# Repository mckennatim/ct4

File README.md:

# setup

```python
import pandas as pd
from importlib import reload
import matplotlib.pyplot as plt
import numpy as np
from IPython.display import display

```

# ct4 ads1115

Design a 4 CT energy monitor for 4 circuits. On hand are a number of 15A/1v and 20A/1v current transformers. When the CT has that kind of designation, the burden resistor is already included. (If not calculate burden resistor below in `ref`)

## ref

* [CT Sensors - Interfacing with an Arduino -OpenEnergyMonitor](https://docs.openenergymonitor.org/electricity-monitoring/ct-sensors/interface-with-arduino.html)
* [Emon Lib - OpenEnergyMonitor](https://github.com/openenergymonitor/EmonLib)
* [KiCad templates for board manufacturers](https://github.com/sethhillbrand/kicad_templates)
* [Esp32-DevKit-V1-DOIT Kicad sym & pretty mod](https://github.com/syauqibilfaqih/ESP32-DevKit-V1-DOIT?tab=readme-ov-file)
* [How to use ADS1115 16 bit ADC module with ESP32](https://www.perceptive-ic.com/news-detailed/How-to-use-ADS1115-16-bit-ADC-module-with-ESP32)

**Best Resources for Explanation:**

1. **Electronics Textbooks:**
   - "The Art of Electronics" by Horowitz & Hill (Chapter 1)
   - "Practical Electronics for Inventors" by Paul Scherz

2. **Online Resources:**
   - **All About Circuits** (allaboutcircuits.com) - Has excellent free tutorials on capacitive reactance and AC coupling
   - **Electronics Tutorials** (electronics-tutorials.ws) - Great explanations with diagrams
   - **Khan Academy** - Physics section on capacitors and RC circuits
   - **MIT OpenCourseWare** - Circuit theory courses

3. **YouTube Channels:**
   - ElectroBOOM
   - EEVblog
   - GreatScott! 

# Circuit
## parts
* esp32 devkit v1 30 pin - (DOIT)
per CT
* [CT SCT013 5A/1v](https://www.amazon.com/dp/B0C33N6NBS?ref_=ppx_hzsearch_conn_dt_b_fed_asin_title_1&th=1)
* [3.5mm audio jack socket 3pin](https://www.amazon.com/dp/B07KY7XX34?ref=ppx_yo2ov_dt_b_fed_asin_title&th=1)
* [10uf ceramic capacitor](https://www.amazon.com/dp/B0D2GVNDHY?ref=ppx_yo2ov_dt_b_fed_asin_title)
* (2)10k Resistor 10k (10k-470K)
* 1.2K Resistor
* 1K resistor
* [4 PCS ADS1115 16 Bit 16 Byte 4 Channel I2C IIC Analog-to-Digital ADC PGA Converter with Programmable Gain Amplifier](https://www.amazon.com/Qoroos-Converter-Programmable-Amplifier-Development/dp/B0DP43DDZG/ref=sr_1_3?crid=1N2VN2M5C7SEH&dib=eyJ2IjoiMSJ9.AjSKy21MIMxKduv00iytPPR8ImZpgHmwBb5A1cFqscTxcAdnr2o4j2pA87-oJvZMAupVzJ1cZdaBISYqlmQK72bHAzZvHIu_Ul1BXsxr0Ga47gktMtuJMsw2a-FLXGbLj6duQmaAjGHtiZ_y-Q9s7spaIWNwSwlrXyMFq1jRz8TATR6x6aGh6kB8im-D9IibKm7X9F9AabMK1pQYwYabQY_1zsgP2wGSbx_TX1pdtHctmHanpSyjwD76ifpGruUP4kvZeqAnUFkIVLvbUjAd7yvjmxbllXPp5-lfmdfic80.4kDcOnx3XfxtRnF8LIIkP8Xf7BBT3MkpKO3g37EqlIk&dib_tag=se&keywords=ads1115&qid=1765291991&s=industrial&sprefix=ads1115%2Cindustrial%2C112&sr=1-3&th=1)
* [LM4040](https://www.mouser.com/ProductDetail/Texas-Instruments/LM4040DIZ-2.5-NOPB?qs=QbsRYf82W3G0BUcaFqTmfQ%3D%3D&countryCode=US&currencyCode=USD) [datasheet](https://www.ti.com/lit/ds/symlink/lm4040-n.pdf?ts=1765232544562&ref_url=https%253A%252F%252Fwww.ti.com%252Fproduct%252FLM4040-N%253Futm_source%253Dgoogle%2526utm_medium%253Dcpc%2526utm_campaign%253Dapp-lp-null-44700045336317407_prodfolderdynamic-cpc-pf-google-ww_en_int%2526utm_content%253Dprodfolddynamic%2526ds_k%253DDYNAMIC+SEARCH+ADS%2526DCM%253Dyes%2526gclsrc%253Daw.ds%2526gad_source%253D1%2526gad_campaignid%253D8020668601%2526gclid%253DEAIaIQobChMIo_WIvIOvkQMVJidECB0IfQOQEAAYASAAEgKZ0PD_BwE)

### notes on pcb order
*lots of holes too big

## design

### test known currents, read CT output

Consider the current range of the heatpump we want to monitor.

```python
# unit label data
total_A = 10.9
compressor_A = 9.2
fan_A = .3
ampacity = 13.2
indoor_Fan_A = .35
indoor_model = "ASUH09KTAS"
indoor_serial = "LDA000334"
outdoor_model = "AOUH09KTAP1"
outdoor_serial = "LDN000103"
```

Test (120V) hair drier, fan, immersion blender and jig saw to find mV produced by sensor, for each current produced as measured by clamp on current meter.

### plot A vs mV

```python
# fan: fh,fl immersion blender: im, hairdrier lo hi, cool, warm, hi: dlc, dlw, dlh, dlh, dhh
sources = ["fh","fl+im", "dlc", "dhc", "dhc+fh+im", "dlw", "dlw+fh+im", "dlh", "dlh+fh+im" "dhh"]
known_A1 = [.48, .75, 1.04, 1.75, 2.39, 3.90, 4.45, 6.65, 7.12, 8.25, 11.93]
known_A2 = [.54, .71, 1.04, 1.75, 2.39, 3.99, 4.52, 6.77, 7.25, 8.36, 12.15]
known_A3 = [.48, 1.0, 1.72, 2.06, 3.88, 6.72, 7.38, 9.88, 12.02, 12.4, 13.31]
mv_A1 = [36, 54,72, 121, 165, 268, 306, 448, 478, 554, 821]
mv_A2 = [78, 110, 141, 238, 328, 517, 600, 723, 810, 920, 1665]
mv_A3 = [53, 108, 183, 219, 406, 684, 778, 1037, 1264, 1305, 1391]
df1 = pd.DataFrame({"A": known_A1, "mv": mv_A1})
df2 = pd.DataFrame({"A": known_A2, "mv": mv_A2})
df3 = pd.DataFrame({"A": known_A3, "mv": mv_A3})
coeffs1 = np.polyfit(df1["A"], df1["mv"], 1)
coeffs2 = np.polyfit(df2["A"], df2["mv"], 1)
coeffs3 = np.polyfit(df3["A"], df3["mv"], 1)
poly1 = np.poly1d(coeffs1)
poly2 = np.poly1d(coeffs2)
poly3 = np.poly1d(coeffs3)
print("Calibration Polynomial 1 (A1): ")
print(poly1)
print("Calibration Polynomial 2 (A2): ")
print(poly2)
print("Calibration Polynomial 3 (A3): ")
print(poly3)
print(poly2)
def A_to_mv1(A):
    return poly1(A)
def A_to_mv2(A):
    return poly2(A)
def A_to_mv3(A):
    return poly3(A)

def plot_calibration_reversed():
    x = np.linspace(0, 13, 100)
    y1 = poly1(x)
    y2 = poly2(x)
    y3 = poly3(x)
    plt.plot(df1["A"], df1["mv"], "o", label="Known A1")
    plt.plot(df2["A"], df2["mv"], "o", label="Known A2")
    plt.plot(df3["A"], df3["mv"], "o", label="Known A3")
    plt.plot(x, y1, "-", label="Calibration A1")
    plt.plot(x, y2, "-", label="Calibration A2")
    plt.plot(x, y3, "-", label="Calibration A3")
    plt.xlabel("Amps")
    plt.ylabel("mV")
    plt.title("Current Sensor Calibration (Reversed Axes)")
    plt.legend()
    plt.grid()
    plt.show()
plot_calibration_reversed() 
    plt.plot(df2["A"], df2["mv"], "o", label="Known A2")
    plt.plot(x, y1, "-", label="Calibration A1")
    plt.plot(x, y2, "-", label="Calibration A2")
    plt.xlabel("Amps")
    plt.ylabel("mV")
    plt.title("Current Sensor Calibration (Reversed Axes)")
    plt.legend()
    plt.grid()
    plt.show()
plot_calibration_reversed()
print(coeffs1)
```

      Cell In[11], line 50
        plt.plot(df2["A"], df2["mv"], "o", label="Known A2")
        ^
    IndentationError: unexpected indent

```python
sources = ["fh","fl+im", "dlc", "dhc", "dhc+fh+im", "dlw", "dlw+fh+im", "dlh", "dlh+fh+im", "dhh"]
known_A1 = [.48, .75, 1.04, 1.75, 2.39, 3.90, 4.45, 6.65, 7.12, 8.25, 11.93]
known_A2 = [.54, .71, 1.04, 1.75, 2.39, 3.99, 4.52, 6.77, 7.25, 8.36, 12.15]
known_A3 = [.48, 1.0, 1.72, 2.06, 3.88, 6.72, 7.38, 9.88, 12.02, 12.4, 13.31]
mv_A1 = [36, 54,72, 121, 165, 268, 306, 448, 478, 554, 821]
mv_A2 = [78, 110, 141, 238, 328, 517, 600, 723, 810, 920, 1665]
mv_A3 = [53, 108, 183, 219, 406, 684, 778, 1037, 1264, 1305, 1391]
df1 = pd.DataFrame({"A": known_A1, "mv": mv_A1})
df2 = pd.DataFrame({"A": known_A2, "mv": mv_A2})
df3 = pd.DataFrame({"A": known_A3, "mv": mv_A3})
coeffs1 = np.polyfit(df1["A"], df1["mv"], 1)
coeffs2 = np.polyfit(df2["A"], df2["mv"], 1)
coeffs3 = np.polyfit(df3["A"], df3["mv"], 1)
poly1 = np.poly1d(coeffs1)
poly2 = np.poly1d(coeffs2)
poly3 = np.poly1d(coeffs3)
print("Calibration Polynomial 1 (A1): ")
print(poly1)
print("Calibration Polynomial 2 (A2): ")
print(poly2)
print("Calibration Polynomial 3 (A3): ")
print(poly3)
def A_to_mv1(A):
    return poly1(A)
def A_to_mv2(A):
    return poly2(A)
def A_to_mv3(A):
    return poly3(A)

def plot_calibration_reversed():
    x = np.linspace(0, 13, 100)
    y1 = poly1(x)
    y2 = poly2(x)
    y3 = poly3(x)
    plt.plot(df1["A"], df1["mv"], "o", label="Known A1")
    plt.plot(df2["A"], df2["mv"], "o", label="Known A2")
    plt.plot(df3["A"], df3["mv"], "o", label="Known A3")
    plt.plot(x, y1, "-", label="Calibration A1")
    plt.plot(x, y2, "-", label="Calibration A2")
    plt.plot(x, y3, "-", label="Calibration A3")
    plt.xlabel("Amps")
    plt.ylabel("mV")
    plt.title("Current Sensor Calibration (Reversed Axes)")
    plt.legend()
    plt.grid()
    plt.show()
plot_calibration_reversed()
print(coeffs1)
```

    Calibration Polynomial 1 (A1): 
     
    67.85 x + 1.626
    Calibration Polynomial 2 (A2): 
     
    123.6 x + 1.254
    Calibration Polynomial 3 (A3): 
     
    104.7 x + 0.9221

    [67.85287623  1.62603625]

```python
# y = mx + b
m = 104.7
b = .9221

x = 10.9
y = 800 

c = (y-b)/m
print(f"Calculated current for {y:0.2f} mV: {c:0.2f} A")
```

    Calculated current for 800.00 mV: 7.63 A

#### understand concepts
The 1uF capacitor on S blocks the DC component of the bias voltage from dragging down and shorting out through the 53ohm internal R of the CT (as measured at the pins)

The **load impedance** isn't just the 53Ω CT - it's the **parallel combination** of:
- CT:  53Ω
- R1 || R2: 82kΩ || 153kΩ ~ 53K

Since 60kΩ >> 53Ω, the AC impedance is essentially **53Ω**.

But actually, for the **cutoff frequency**, what matters is the impedance that C1 sees:

**C1 sees:** CT (53Ω) in series with [R1 || R2] = 53Ω + 53kΩ ≈ **53kΩ**

#### To pass AC mV (60 Hz) and block the DC
for the **high-pass filter** cutoff, the relevant impedance is the **bias network** (R1||R2 = 53kΩ)

(The 53Ω only matters for loading the voltage divider with AC current, which is minimal with 60kΩ bias resistors. )

**Rule of Thumb:** Choose fc to be 1/10th of your lowest frequency of interest for minimal signal loss.

For fc = 6 Hz: 
C = 1 / (2π × 53,000 × 6) ≈ 0.5 µF
```

Round up to 1uF

#### calculating values

```python
R1 = 82000
R2 = 153000
Rct =53

R1llR2 = (R1*R2)/(R1+R2)
print(f"Parallel resistance of R1 and R2: {R1llR2:0.1f} ohms")  
Vbias = 2.5 * R2 /(R1+R2)
print(f"Bias voltage at divider point: {Vbias:0.3f} V")

Rctll_R1llR2 = (Rct*R1llR2)/(Rct+R1llR2)
print(f"Total resistance seen at bias point with load: {Rctll_R1llR2:0.1f} ohms")

fc = 6  # hz 1/10 of 60hz
C1 = 1 / (2*3.14159 * R1llR2 * fc)

print(f"Capacitance needed: {C1*1e6:0.2f} uF")

```

    Parallel resistance of R1 and R2: 53387.2 ohms
    Bias voltage at divider point: 1.628 V
    Total resistance seen at bias point with load: 52.9 ohms
    Capacitance needed: 0.50 uF

### R controlling current through the lm4040
To account for the load, you need to ensure the resistor provides enough current for both the LM4040’s minimum operating current and the current drawn by your voltage divider (and any other load).

1. Calculate the current your voltage divider (and any other load) will draw from the reference:
   $$
   I_{load} = \frac{2.5\,V}{R_{divider}}
   $$
2. Add the LM4040’s minimum required current (from the datasheet, e.g., 60 µA):
   $$
   I_{total} = I_{load} + I_{min}
   $$
3. Calculate the resistor value:
   $$
   R = \frac{V_{in} - V_{ref}}{I_{total}}
   $$

Choose the next lower standard value to ensure enough current (e.g., 10 kΩ).

```python
Iload = 2.5/(100000+150000)
print(f"Load current through resistor: {Iload*1000} mA")
Imin = 60e-6
print(f"Minimum current through resistor with load: {Imin*1000:0.3f} mA")
Itotal = Imin + Iload
print(f"Total current through resistor with load: {Itotal*1000:0.3f} mA")
R=(3.3-2.5)/Itotal
print(f"Resistor value to set minimum current with load: {R:0.1f} ohms")

```

    Load current through resistor: 0.01 mA
    Minimum current through resistor with load: 0.060 mA
    Total current through resistor with load: 0.070 mA
    Resistor value to set minimum current with load: 11428.6 ohms

## fixing the toolchain

Changed the default terminal in vscode to cmd. cmd-shift-p Terminal:Select default profile

cmd couldn't find `where python`
* "C:\Users\mcken\.platformio\penv\Scripts" needed to be added to system path 
  * windows search env...Edit environmental Variables, find path in system variables and add to the path

Platformio uses its own penv python. It complained about missing a library. Since cmd uses conda, pip would have used the active conda env pip and put it in the wrong place. To use Platformio's python: 
* C:\Users\mcken\.platformio\penv\Scripts\python.exe -m pip install intelhex

from cmd run `platformio system info` to see where python is and it is

### remember to hold the boot button on esp32's
A fatal error occurred: Failed to connect to ESP32: Wrong boot mode detected (0x13)! The chip needs to be in download mode
* Hold down the “BOOT” button on your ESP32 board.
* While holding “BOOT”, click “Upload” in PlatformIO/VSCode.
* Keep holding “BOOT” until you see the upload progress start (dots or percentage in the terminal).
* Release “BOOT” after the upload starts.

    CONFIGURATION: https://docs.platformio.org/page/boards/espressif32/esp32doit-devkit-v1.html
    PLATFORM: Espressif 32 (6.12.0) > DOIT ESP32 DEVKIT V1
    HARDWARE: ESP32 240MHz, 320KB RAM, 4MB Flash

## esp32 dev kit1 pinout

## software setup 1

declare functions defined later before setup

### calibrateZeroOffset()

Take 500 samples: zeroOffsetADC is the average of the digital counts of the ADC at 0V

zeroOffsetADC = sum / numSamples;

For the ADS1115, each count at GAIN_ONE (±4.096 V) is 0.125 mV

Calibrating zero offset... ensure CT is not measuring any current

Zero offset calibrated: 12895.45 ADC counts

This corresponds to: 1.612 V bias

```python
counts0 = 12895.45
volts0 = counts0 * 0.000125
print(f"Zero offset: {counts0:0.2f} counts = {volts0:0.3f} V")
```

    Zero offset: 12895.45 counts = 1.612 V

```python
counts7_1A = 10704
volts7_1A = .734
x = volts7_1A / counts7_1A
print(f"x = {x:0.8f},{x*2:0.8f}")
```

    x = 0.00006857,0.00013714

```python
cz= 16
vz=.0000015
x = vz/cz
print(f"x = {x:0.8f},{x*2:0.8f}") 
```

    x = 0.00000009,0.00000019

# esp32 code for ct4
goto [ct4.ipynb](../ct4/esp-ct4/ct4.ipynb) for specific info

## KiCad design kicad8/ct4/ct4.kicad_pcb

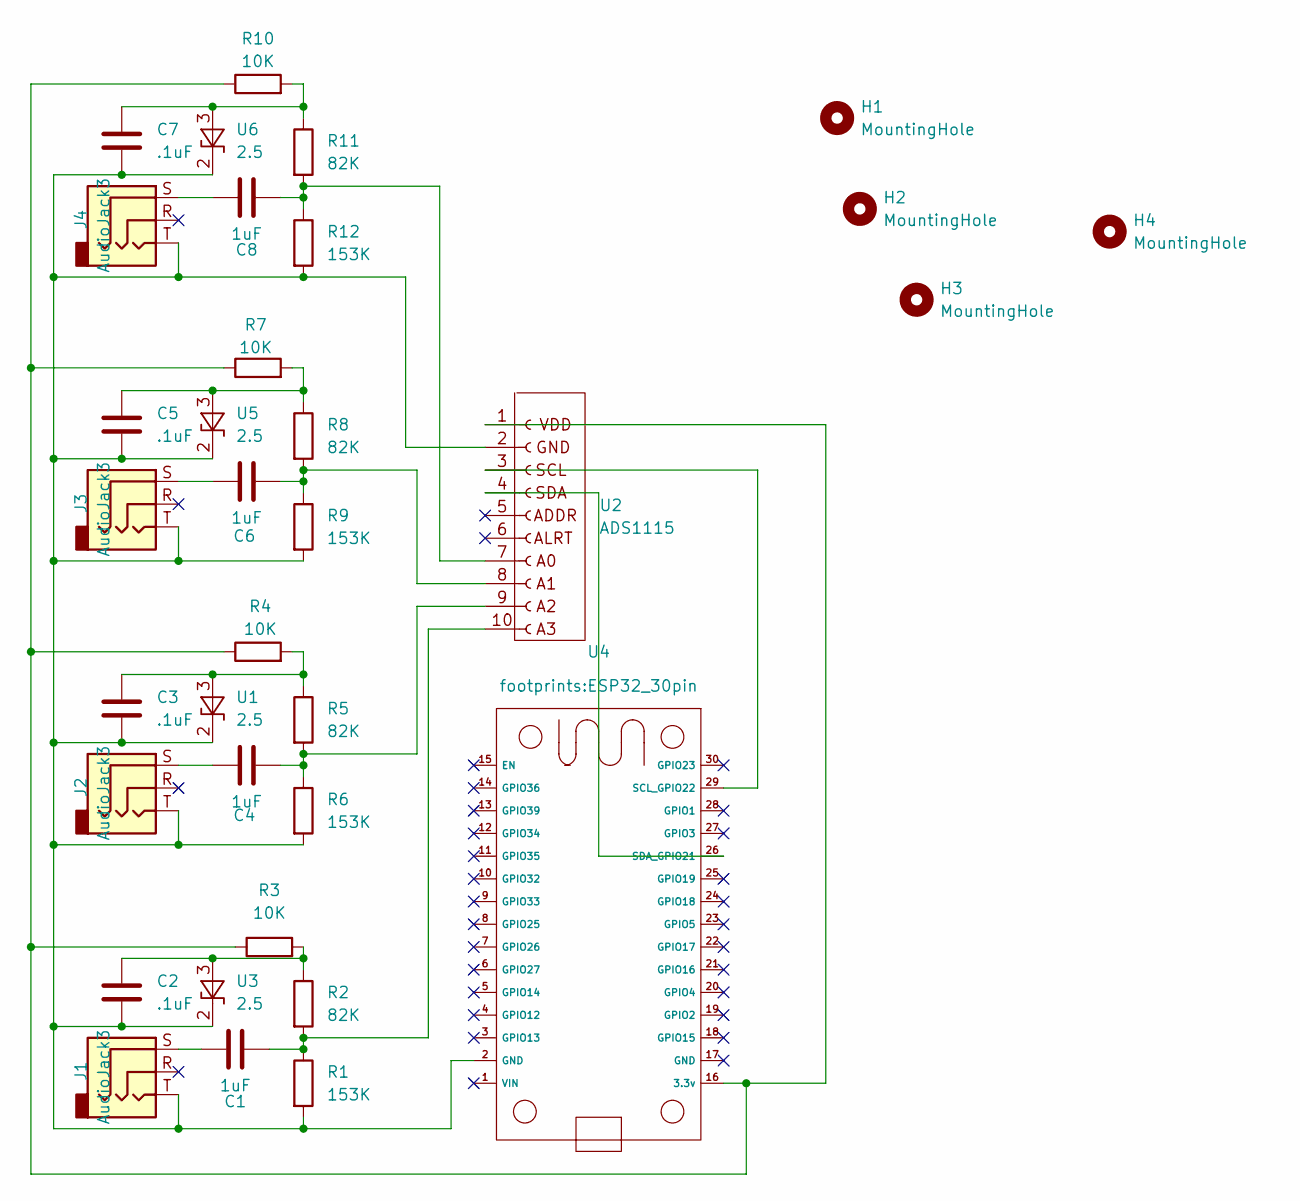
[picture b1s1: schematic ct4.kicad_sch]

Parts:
C1, C4, C6, C8: 1uF; C_Disc_D7.5mm_W5.0mm_P5.00mm
C2, C3, C5, C7: .1uF; C_Disc_D7.5mm_W5.0mm_P5.00mm
H1, H2, H3, H4: MountingHole; MountingHole_3.5mm
J1, J2, J3, J4: AudioJack3; audiojack_female_3pin_3.5mm
R1, R6, R9, R12: 153K; R_Axial_DIN0204_L3.6mm_D1.6mm_P7.62mm_Horizontal
R2, R5, R8, R11: 82K; R_Axial_DIN0204_L3.6mm_D1.6mm_P7.62mm_Horizontal
R3, R4, R7, R10: 10K; R_Axial_DIN0204_L3.6mm_D1.6mm_P7.62mm_Horizontal
U1, U3, U5, U6: 2.5; TO-92_Inline
U2: ADS1115; ADC1115_ADC_Module
U4: ESP32_30pin

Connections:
unnamed: C1.1, J1.S
unnamed: C4.1, J2.S
unnamed: C6.1, J3.S
unnamed: C8.1, J4.S
unnamed: C3.2, R4.2, R5.1, U1.3 (A)
unnamed: C2.1, C3.1, C5.1, C7.1, J1.T, J2.T, J3.T, J4.T, R1.2, R6.2, R9.2, R12.2, U1.2 (K), U2.2, U3.2 (K), U4.2 (GND), U5.2 (K), U6.2 (K)
unnamed: R3.1, R4.1, R7.1, R10.1, U2.1, U4.16 (3.3v)
unnamed: U2.3, U4.29 (SCL_GPIO22)
unnamed: U2.4, U4.26 (SDA_GPIO21)
unnamed: C8.2, R11.2, R12.1, U2.7
unnamed: C6.2, R8.2, R9.1, U2.8
unnamed: C4.2, R5.2, R6.1, U2.9
unnamed: C1.2, R1.1, R2.2, U2.10
unnamed: C2.2, R2.1, R3.2, U3.3 (A)
unnamed: C5.2, R7.2, R8.1, U5.3 (A)
unnamed: C7.2, R10.2, R11.1, U6.3 (A)

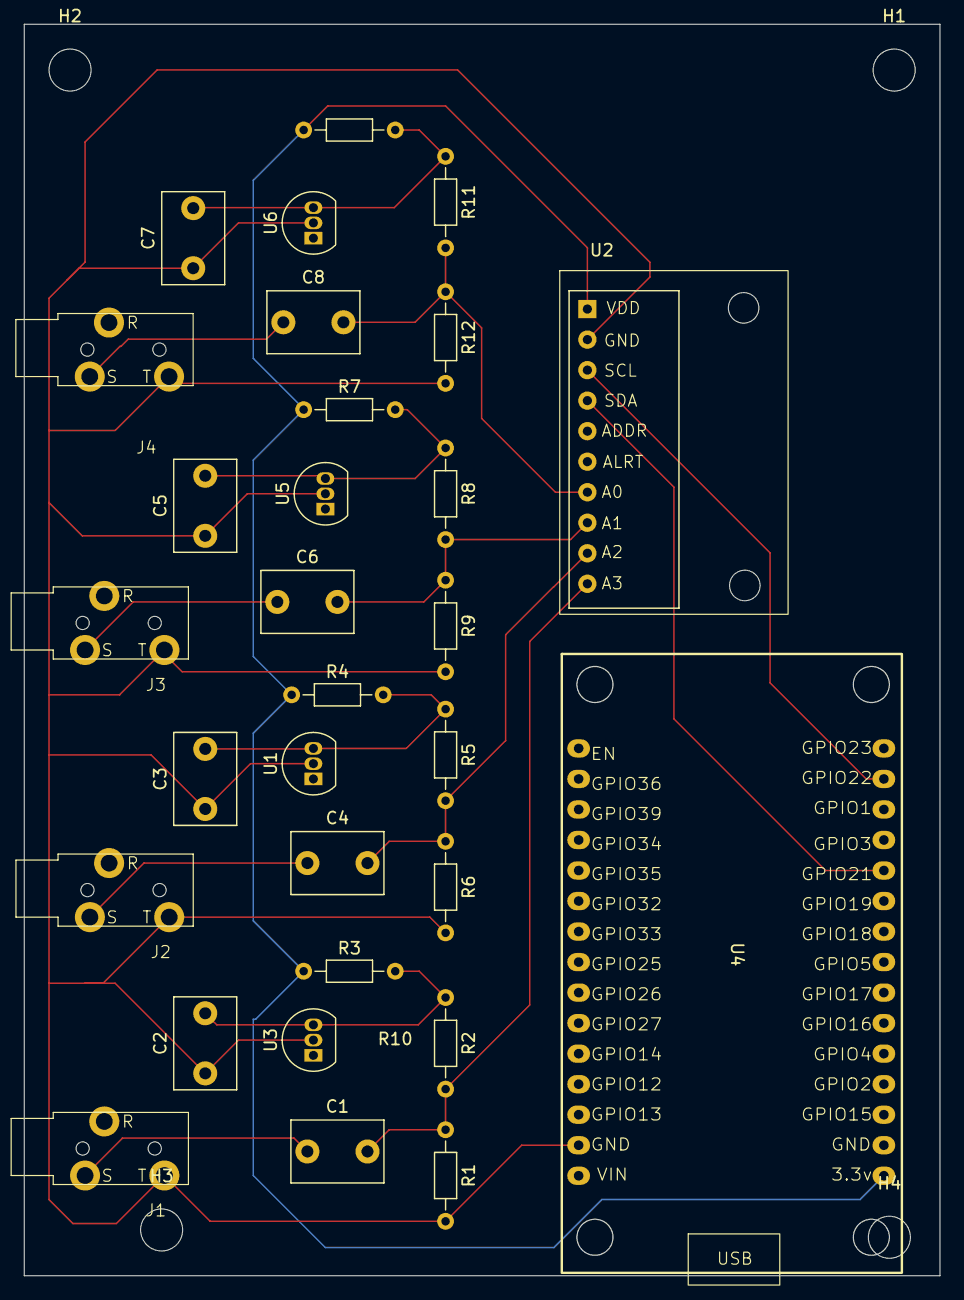
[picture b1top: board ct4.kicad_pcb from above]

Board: 4 copper layers, 76.2 x 104.1 mm, 34 parts (0 on the bottom side), 16 nets.

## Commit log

2026-01-25 01-separation_of_concerns
2026-01-28 02-onWIFI
2026-01-28 03-onWIFI-MQTTworks
2026-01-29 compiles but doesn't seem to get sensor readings, something is off in the timing
2026-01-30 04-Mqtt_connects-Current_correct-code_not_reviewed
2026-02-02 04-main_loop_not_clean
2026-02-02 05-main_loop_not_clean
2026-02-04 06-readsCurrent_sendsMQTT_sloppy_serialPrint
